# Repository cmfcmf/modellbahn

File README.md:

# Modellbahn

Eine Sammlung von Hardware und Software, die ich auf meiner Modelleisenbahnanlage verwende.

Eine Übersicht über alle Projekte ist hier zu finden: https://cmfcmf.github.io/modellbahn.

Lokal kann man die Website folgendermaßen bauen:

    bundle exec jekyll serve --livereload

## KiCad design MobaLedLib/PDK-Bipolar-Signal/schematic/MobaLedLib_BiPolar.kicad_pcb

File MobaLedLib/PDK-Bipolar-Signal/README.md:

---
layout: project
tags: [padauk, signale, mobaledlib]
permalink: mobaledlib/bipolar-led-driver-pdk
state: finished
---

# MobaLedLib PFS173 Bipolar LED Driver

| Oberseite                   | Unterseite                       |
| --------------------------- | -------------------------------- |
| |  |

Bei diesem Projekt handelt es sich um einen Treiber-Baustein für bipolare LEDs, wie sie z.B. in den Märklin Hobby-Signalen verwendet werden.
Wir benutzen einen sehr kostengünstigen [PFS173](https://free-pdk.github.io/chips/PFS173) Mikrocontroller um das PWM-Signal des roten und grünen Kanals eines WS2811 zu lesen.
Basierend auf diesem Signal generiert der Mikrocontroller an zwei Pins ein komplementäres PWM-Signal.
An diese beiden Ausgänge kann dann eine bipolare LED angeschlossen werden.

Die vier Ausgänge auf der linken Seite des Moduls sind wiefolgt belegt:

| Ausgang   | Funktion                                                      |
| --------- | ------------------------------------------------------------- |
| 1 (oben)  | rote LED +, grüne LED - (bis 20mA, keine Konstantstromquelle) |
| 2         | rote LED -, grüne LED + (bis 20mA, keine Konstantstromquelle) |
| 3         | 5V                                                            |
| 4 (unten) | blauer Kanal (unverändert, direkt vom WS2811)                 |

Auf dem Board befindet sich eine Heartbeat-LED, die fortwährend blinkt.

{%- include pdf_view.html name="schematic/MobaLedLib_BiPolar-Schematic.pdf" -%}
{%- include pdf_view.html name="schematic/MobaLedLib_BiPolar-PCB.pdf" -%}

## Programmierung

Der Mikrocontroller ist mit der [Free-PDK Toolchain](https://free-pdk.github.io/) programmiert.
Zusätzlich benötigt werden die Include-Files von [hier](https://github.com/free-pdk/pdk-includes) und [hier](https://github.com/free-pdk/easy-pdk-includes).

## Lizenz

GPLv2, wobei die Dateien im "code/includes" Ordner von [hier](https://github.com/free-pdk/free-pdk-examples/tree/master/include) stammen.

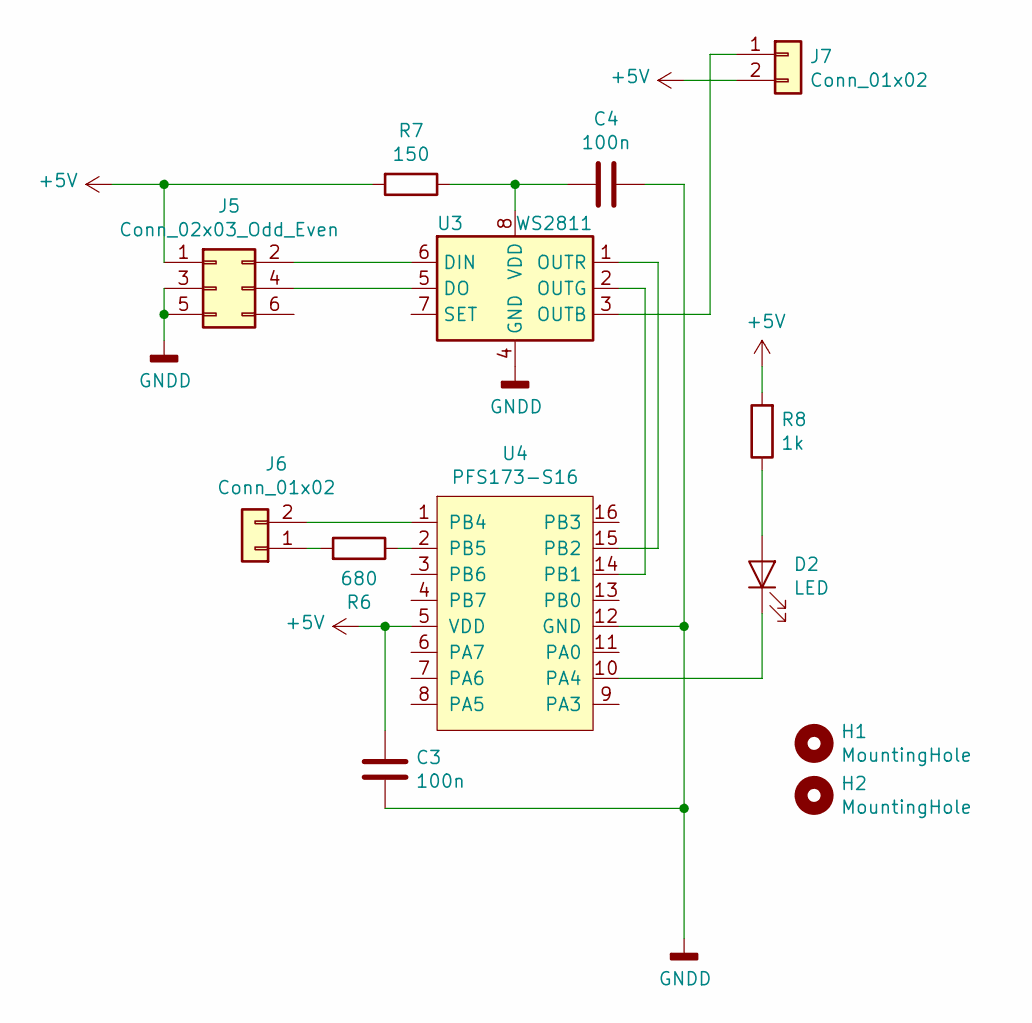
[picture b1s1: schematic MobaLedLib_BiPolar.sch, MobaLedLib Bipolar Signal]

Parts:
C3, C4: 100n; C_Disc_D4.7mm_W2.5mm_P5.00mm
D2: LED; LED_D3.0mm
H1, H2: MountingHole; MountingHole_3.2mm_M3_ISO7380
J5: Conn_02x03_Odd_Even; IDC-Header_2x03_P2.54mm_Vertical
J6, J7: Conn_01x02; TerminalBlock_bornier-2_P5.08mm
R6: 680; R_Axial_DIN0204_L3.6mm_D1.6mm_P2.54mm_Vertical
R7: 150; R_Axial_DIN0204_L3.6mm_D1.6mm_P7.62mm_Horizontal
R8: 1k; R_Axial_DIN0204_L3.6mm_D1.6mm_P2.54mm_Vertical
U3: WS2811; DIP-8_W7.62mm_Socket_LongPads
U4: PFS173-S16; DA04-11SEKWA

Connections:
+5V: C3.1, J5.1, J7.2, R7.2, R8.2, U4.5 (VDD)
GNDD: C3.2, C4.1, J5.3, J5.5, U3.4 (GND), U4.12 (GND)
unnamed: C4.2, R7.1, U3.8 (VDD)
unnamed: D2.1 (K), U4.10 (PA4)
unnamed: D2.2 (A), R8.1
unnamed: J5.2, U3.6 (DIN)
unnamed: J5.4, U3.5 (DO)
unnamed: J6.1, R6.2
unnamed: J6.2, U4.1 (PB4)
unnamed: J7.1, U3.3 (OUTB)
unnamed: R6.1, U4.2 (PB5)
unnamed: U3.1 (OUTR), U4.15 (PB2)
unnamed: U3.2 (OUTG), U4.14 (PB1)

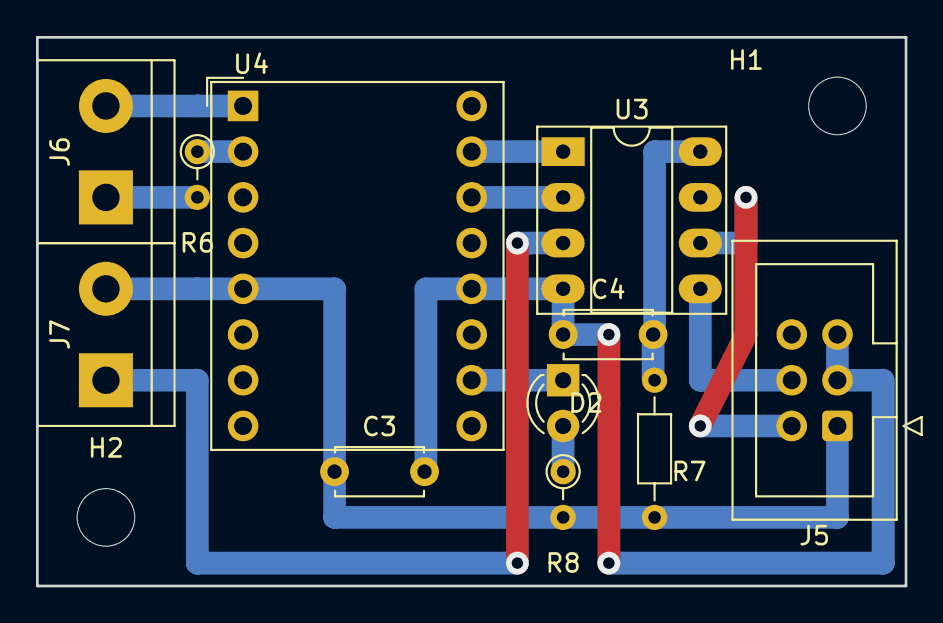
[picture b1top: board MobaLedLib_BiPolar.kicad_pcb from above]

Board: 2 copper layers, 48.3 x 30.5 mm, 13 parts (0 on the bottom side), 13 nets.

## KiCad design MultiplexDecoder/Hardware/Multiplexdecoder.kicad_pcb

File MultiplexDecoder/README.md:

---
layout: project
tags: [arduino, arduino nano, decoder, signale, viessmann, dcc]
permalink: decoder/multiplex
state: wip
related_projects: [signale/multiplex]
---

# Decoder für Viessmann Multiplex-Signale

Es handelt sich um einen DCC-Decoder für 4 Multiplex-Signale von Viessmann.
Der Decoder basiert auf einem Arduino Nano.

## Funktionen

- Ansteuerung von bis zu 4 HV-Signalen, jeweils optional mit Vorsignal am Mast
  - KS-Signale wären theoretisch auch möglich, sind aber noch nicht implementiert, da ich keine zum Testen da habe
- Automatische Erkennung der Signaltypen beim Einschalten
- Alle Signalbilder schaltbar, inklusive "dunkel"
- Sanftes Überblenden zwischen den Signalbildern
- Steuerung über DCC-Weichenbefehle
- Separate Adressen pro Signal und Vorsignal

### Adresseinstellung

1. ggf. neue Signale anschließen und den Dekoder neu starten,
   indem der Reset-Knopf auf der Arduino-Platine gedruckt wird.
   Dadurch werden die neu angeschlossenen Signale erkannt.
2. Es darf nun kein Fahrbetrieb mehr stattfinden und keine (anderen) Weichen und Signale geschaltet werden!
3. Den Adressprogrammierknopf einmal drücken -> die LED auf der Platine fängt an zu blinken.
4. Das erste angeschlossene Hauptsignal fängt an, nacheinander alle Signalbilder durchzuschalten.
5. Möchte man die Adresse des Signals nicht ändern, drückt man einfach den Adressprogrammierknopf nochmal.
   Andernfalls sendet man einen Weichenbefehl mit der Digitalzentrale. Das Signal übernimmt dann die gesendete Adresse.
6. Jetzt fängt das nächste Signal an alle Signalbilder durchzuschalten. War am Mast des Hauptsignals ein
   Vorsignal angeschlossen, fängt dieses an die Signalbilder durchzuschalten.
7. Nun sendet man die Adresse des nächsten Signals wie in Schritt 5 beschrieben.
8. Wenn alle angeschlossenen Signale neue Adressen erhalten haben, hört die LED auf der Platine auf zu blinken.

## Hardware

Der Schaltplan ist sehr einfach gehalten und bietet Anschlussmöglichkeiten für sowohl
die Stecker der Viessmann-Signale als auch eigene Verlängerungsleitungen. In allen
Signalleitungen sind 680Ω-Widerstände verbaut. Damit leuchten die Signale immer noch
sehr hell. Das DCC-Signal wird über einen 6N137-Optokoppler eingelesen.
Die Stromversorgung geschieht an einem separaten Eingang über einen Gleichrichter
mit nachgeschaltetem 7805-Linearregler. Man kann beide Eingänge auch parallel schalten,
wenn man keine separate Stromversorgung benutzen möchte.
Der Programmierknopf ist an A6 angeschlossen. Da dieser Eingang nicht über einen
internen Pull-Up-Widerstand verfügt, ist dieser extern vorgesehen.

{%- include pdf_view.html name="Hardware/Multiplexdecoder.pdf" -%}

Eine abgespeckte Version der Platine habe ich derzeit auf Lochraster aufgebaut.
Aufgrund der einfachen Schaltung ging das flott von der Hand. Eine "professionell"
gelayoutete Platine habe ich ebenfalls erstellt, aber noch nicht fertigen lassen
(der Arduino fehlt im 3D-Bild):

{%- include image_view.html name="Hardware/Multiplexdecoder.png" -%}

## Software

Die Software ist für die Arduino-IDE geschrieben und muss mittels dieser in den
Arduino Nano übertragen werden. Falls die Übertragung nicht funktioniert, sollte
man nochmal sichergehen, dass im Menü unter `Werkzeuge -> Board` `Arduino Nano`
ausgewählt und unter `Werkzeuge -> Prozessor` `Atmega328P` oder `Atmega328P (Old Bootloader)`
ausgewählt ist. Ob der Bootloader des Arduinos neu oder "old" ist, lässt sich
am besten durch probieren herausfinden; wenn die Übertragung klappt, hat man
den richtigen Eintrag ausgewählt.

### Konfigurationsoptionen

Einige Optionen sind nur beim Programmieren des Arduinos und nicht im
späteren Betrieb einstellbar. Die notwendigen Einstellungen befinden sich
allesamt in der `Config.h`-Datei und müssen angepasst werden, bevor der
Arduino programmiert wird.

- **DEMO**
  - **0**: Normaler Betrieb
  - **1**: Demomodus aktiv: Alle Signale schalten nacheinander automatisch ihre Signalbegriffe durch.
  - **2**: Demomodus aktiv: Alle Signale schalten zufällige Signalbegriffe durcheinander.
- **DARK_MAIN_SIGNAL_ASPECT**
  - **0**: Hauptsignale können nicht dunkel geschaltet werden.
  - **1**: Hauptsignale können zusätzlich dunkel geschaltet werden.
- **DARK_DISTANT_SIGNAL_ASPECT**
  - **0**: Vorsignale können nicht dunkel geschaltet werden
    (**steht das Hauptsignal auf rot, wird das Vorsignal aber in jedem Fall dunkel geschaltet!**).
  - **1**: Vorsignale können zusätzlich dunkel geschaltet werden.
- **USE_SERIAL**
  - **0**: Keine Debug-Ausgaben über den seriellen Anschluss.
  - **1**: Zusätzliche Debug-Ausgaben über den seriellen Anschluss.

{%- include code_view.html name="Config.h" from_line=4 to_line=8 -%}

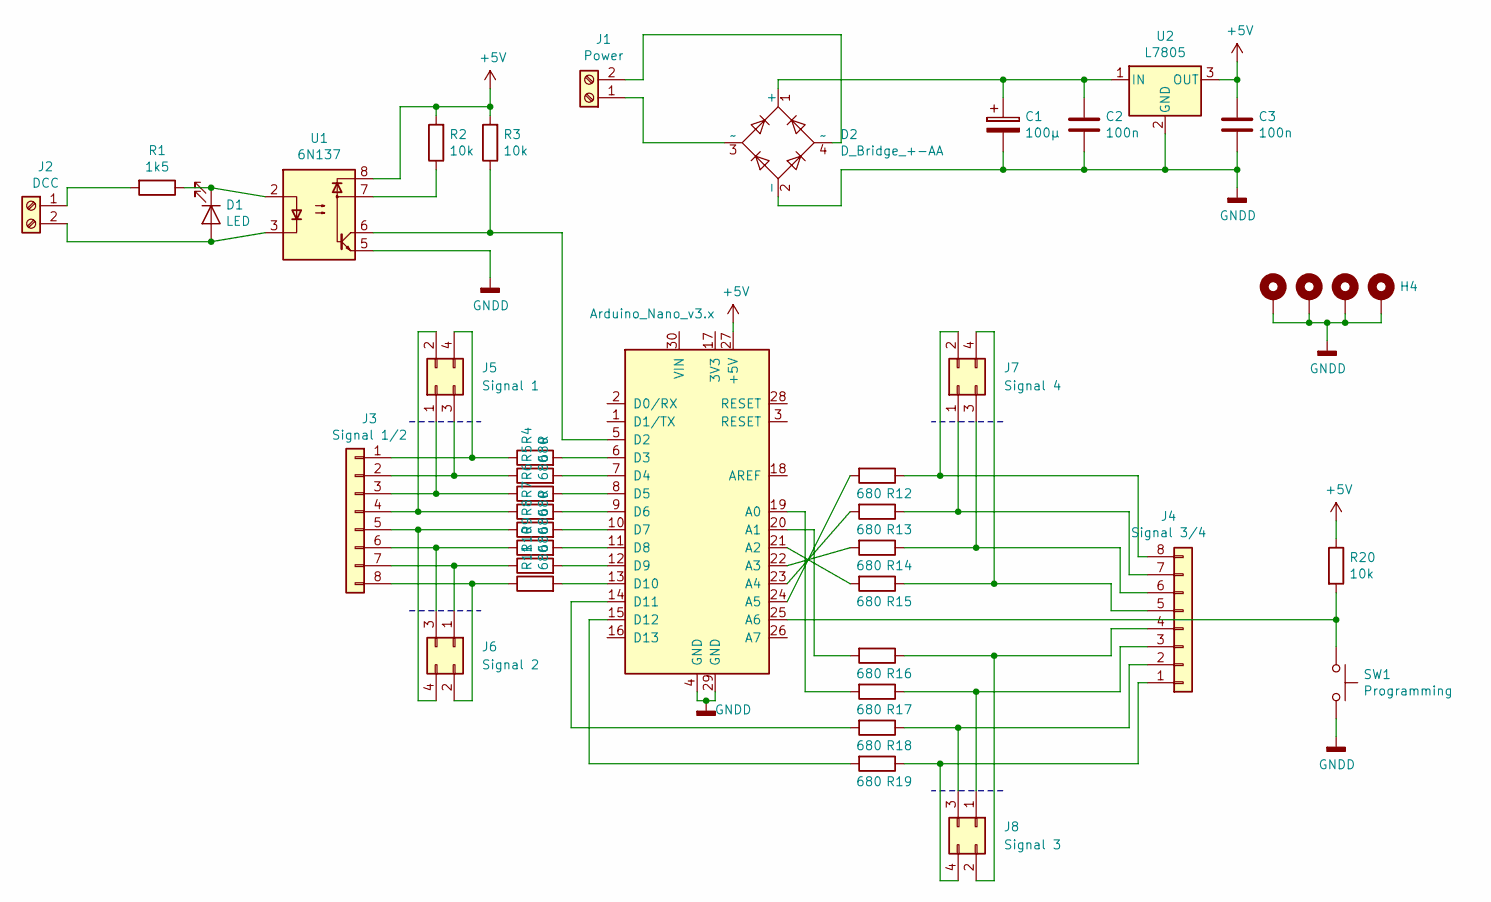
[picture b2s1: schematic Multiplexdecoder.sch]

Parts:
A1: Arduino_Nano_v3.x; Arduino_Nano
C1: 100µ; CP_Radial_D10.0mm_P5.00mm
C2, C3: 100n; C_Disc_D4.3mm_W1.9mm_P5.00mm
D1: LED; LED_D3.0mm
D2: D_Bridge_+-AA; Diode_Bridge_DIP-4_W7.62mm_P5.08mm
H1, H2, H3, H4: MountingHole_Pad; MountingHole_3.2mm_M3_Pad_Via
J1: Power; PhoenixContact_MSTBA_2,5_2-G-5,08_1x02_P5.08mm_Horizontal
J2: DCC; PhoenixContact_MSTBA_2,5_2-G-5,08_1x02_P5.08mm_Horizontal
J3: Signal 1/2; PhoenixContact_MSTBA_2,5_8-G-5,08_1x08_P5.08mm_Horizontal
J4: Signal 3/4; PhoenixContact_MSTBA_2,5_8-G-5,08_1x08_P5.08mm_Horizontal
J5: Signal 1; PinHeader_2x02_P2.00mm_Vertical
J6: Signal 2; PinHeader_2x02_P2.00mm_Vertical
J7: Signal 4; PinHeader_2x02_P2.00mm_Vertical
J8: Signal 3; PinHeader_2x02_P2.00mm_Vertical
R1: 1k5; R_Axial_DIN0204_L3.6mm_D1.6mm_P5.08mm_Horizontal
R2, R3, R20: 10k; R_Axial_DIN0204_L3.6mm_D1.6mm_P5.08mm_Horizontal
R4, R7: R; R_Axial_DIN0204_L3.6mm_D1.6mm_P1.90mm_Vertical
R5, R6, R8, R9, R10, R11, R12, R13, R14, R15, R16, R17, R18, R19: 680; R_Axial_DIN0204_L3.6mm_D1.6mm_P1.90mm_Vertical
SW1: Programming; SW_PUSH_6mm_H5mm
U1: 6N137; DIP-8_W7.62mm
U2: L7805; TO-220-3_Vertical

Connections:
+5V: A1.27 (+5V), C3.1, R2.2, R3.2, R20.1, U1.8, U2.3 (OUT)
GNDD: A1.4 (GND), A1.29 (GND), C1.2, C2.2, C3.2, D2.2 (-), H1.1, H2.1, H3.1, H4.1, SW1.2, U1.5, U2.2 (GND)
unnamed: A1.5 (D2), R3.1, U1.6
unnamed: A1.6 (D3), R4.2
unnamed: A1.7 (D4), R5.2
unnamed: A1.8 (D5), R6.2
unnamed: A1.9 (D6), R7.2
unnamed: A1.10 (D7), R8.2
unnamed: A1.11 (D8), R9.2
unnamed: A1.12 (D9), R10.2
unnamed: A1.13 (D10), R11.2
unnamed: A1.14 (D11), R18.2
unnamed: A1.15 (D12), R19.2
unnamed: A1.19 (A0), R17.2
unnamed: A1.20 (A1), R16.2
unnamed: A1.21 (A2), R15.2
unnamed: A1.22 (A3), R14.2
unnamed: A1.23 (A4), R13.2
unnamed: A1.24 (A5), R12.2
unnamed: A1.25 (A6), R20.2, SW1.1
unnamed: C1.1, C2.1, D2.1 (+), U2.1 (IN)
unnamed: D1.1 (K), R1.1, U1.2
unnamed: D1.2 (A), J2.2, U1.3
unnamed: D2.3 (~~), J1.1
unnamed: D2.4 (~~), J1.2
unnamed: J2.1, R1.2
unnamed: J3.1, J5.4, R4.1
unnamed: J3.2, J5.3, R5.1
unnamed: J3.3, J5.1, R6.1
unnamed: J3.4, J5.2, R7.1
unnamed: J3.5, J6.4, R8.1
unnamed: J3.6, J6.3, R9.1
unnamed: J3.7, J6.1, R10.1
unnamed: J3.8, J6.2, R11.1
unnamed: J4.1, J8.4, R19.1
unnamed: J4.2, J8.3, R18.1
unnamed: J4.3, J8.1, R17.1
unnamed: J4.4, J8.2, R16.1
unnamed: J4.5, J7.4, R15.1
unnamed: J4.6, J7.3, R14.1
unnamed: J4.7, J7.1, R13.1
unnamed: J4.8, J7.2, R12.1
unnamed: R2.1, U1.7

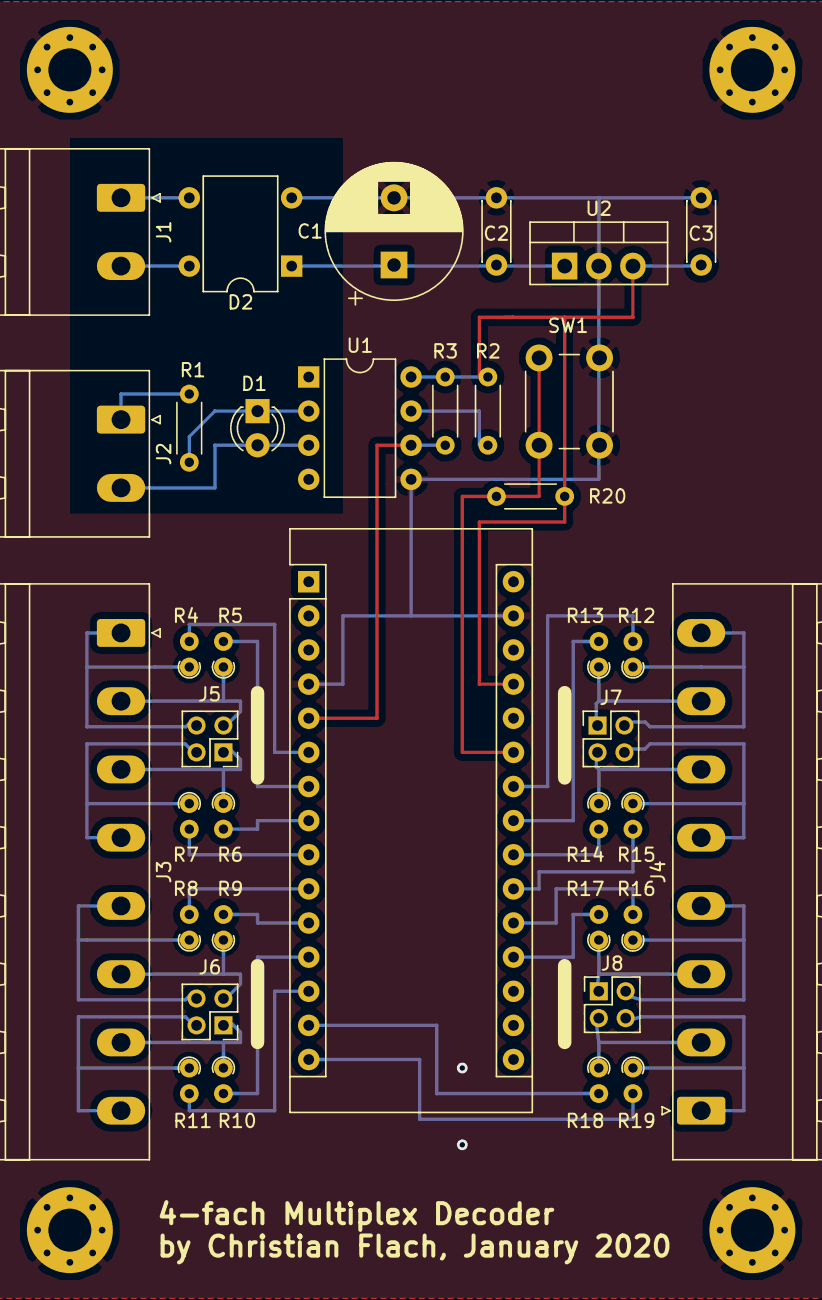
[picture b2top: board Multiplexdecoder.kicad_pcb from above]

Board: 2 copper layers, 41 parts (0 on the bottom side), 43 nets.

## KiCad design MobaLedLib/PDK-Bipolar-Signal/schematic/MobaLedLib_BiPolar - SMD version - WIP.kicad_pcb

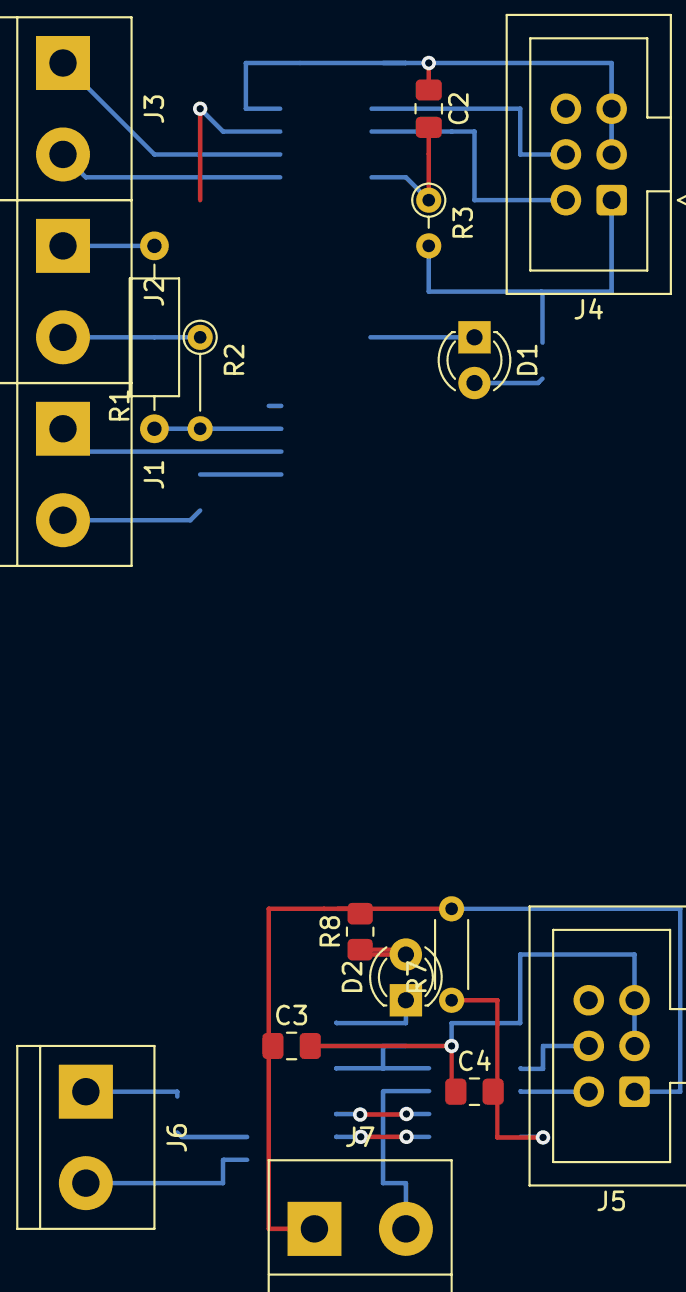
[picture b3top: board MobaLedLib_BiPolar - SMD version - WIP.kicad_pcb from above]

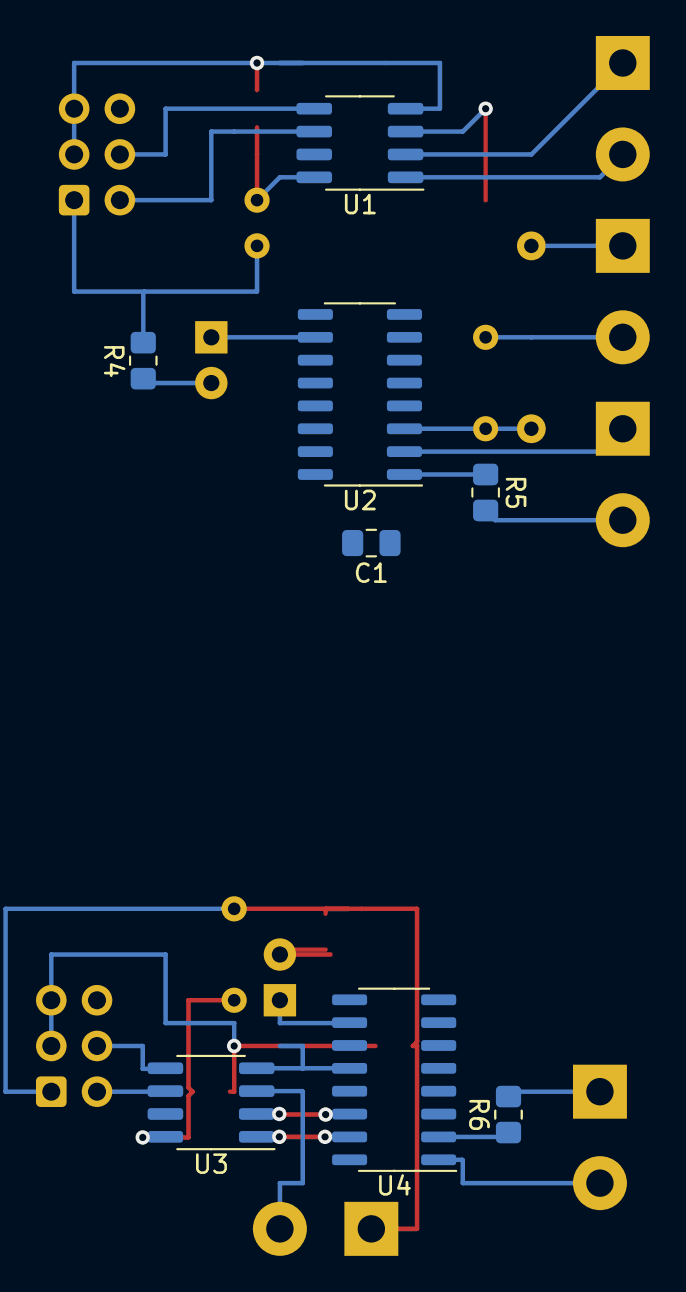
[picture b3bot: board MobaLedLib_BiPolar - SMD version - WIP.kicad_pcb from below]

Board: 2 copper layers, 25 parts (8 on the bottom side), 26 nets.

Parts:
C1, C2, C3, C4: 100n; C_0805_2012Metric_Pad1.18x1.45mm_HandSolder
D1, D2: LED; LED_D3.0mm
J1, J2, J3, J6, J7: Conn_01x02; TerminalBlock_bornier-2_P5.08mm
J4, J5: Conn_02x03_Odd_Even; IDC-Header_2x03_P2.54mm_Vertical
R1: 150k; R_Axial_DIN0207_L6.3mm_D2.5mm_P10.16mm_Horizontal
R2: 22k; R_Axial_DIN0204_L3.6mm_D1.6mm_P5.08mm_Vertical
R3: 150; R_Axial_DIN0204_L3.6mm_D1.6mm_P2.54mm_Vertical
R4, R8: 1k; R_0805_2012Metric_Pad1.20x1.40mm_HandSolder
R5, R6: 680; R_0805_2012Metric_Pad1.20x1.40mm_HandSolder
R7: 150; R_Axial_DIN0204_L3.6mm_D1.6mm_P5.08mm_Horizontal
U1, U3: WS2811; SOP-8_3.76x4.96mm_P1.27mm
U2, U4: PFS173-S16; SOIC-16_3.9x9.9mm_P1.27mm

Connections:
+5V: C3.1, J2.1, J4.1, J5.1, J7.1, R1.2, R3.2, R4.2, R7.2, R8.2, U2.4, U4.5
GNDD: C1.2, C2.1, C3.2, C4.1, J2.2, J4.3, J4.5, J5.3, J5.5, R2.1, U1.4, U2.12, U3.4, U4.12
unnamed: C1.1, U2.5
unnamed: C2.2, R3.1, U1.8
unnamed: C4.2, R7.1, U3.8
unnamed: D1.1, U2.10
unnamed: D1.2, R4.1
unnamed: D2.1, U4.10
unnamed: D2.2, R8.1
unnamed: J1.1, U2.2
unnamed: J1.2, R5.2
unnamed: J3.1, U1.2
unnamed: J3.2, U1.1
unnamed: J4.2, U1.6
unnamed: J4.4, U1.5
unnamed: J5.2, U3.6
unnamed: J5.4, U3.5
unnamed: J6.1, R6.2
unnamed: J6.2, U4.1
unnamed: J7.2, U3.3
unnamed: R1.1, R2.2, U2.3
unnamed: R5.1, U2.1
unnamed: R6.1, U4.2
unnamed: U1.3, U2.13
unnamed: U3.1, U4.15
unnamed: U3.2, U4.14

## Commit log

2019-12-27 Initial commit.
2019-12-27 Add jekyll site
2019-12-27 Infos zur Wagenbeleuchtung
2019-12-27 Fix support for serving from subdirectory
2019-12-27 Use GitHub's STL viewer
2019-12-27 Add mathjax support
2019-12-27 Allgemeines zur Wagenbeleuchtung
2019-12-27 Sortiere Projekte nach Titel
2019-12-29 Minor site improvements
2019-12-29 Add section on multiplex signals
2019-12-29 Fix language, add sitemap
2019-12-29 Add support for project states
2019-12-30 Introduce "related projects"
2019-12-30 Fix typo
2019-12-30 Add privacy policy link
2019-12-30 Import MultiplexDecoder project
2019-12-30 Add code highlighting support
2019-12-30 Performance improvements, do not persist state in demo mode
2019-12-31 Make Serial and dark aspects optional, use watchdog as coarse timer
2019-12-31 Allow separate addresses per signal, improve address programming experience
2019-12-31 Show filename in code box footer
2020-01-01 Detect some file types from file content
2020-01-01 Improve documentation
2020-01-01 Adjust pin mapping for board layout
2020-01-01 Create schematic and pcb with KiCad
2020-01-01 Document hardware
2020-01-04 Split up dimming updates across multiple invocations of the ISR
    This makes it less likely that an INT0 edge may be missed
2020-01-04 Add makefile and proof of concept test using simulavr
2020-01-04 Fix signal aspect order to match what the CS2 expects
2020-01-04 Move templates into .h to be Arduino IDE-compatible
2020-01-05 Add information on dccpp
2020-01-05 Minor fixes
2020-02-06 Add state: finished to Schleppschalter Umbau
2020-02-26 Bump nokogiri from 1.10.7 to 1.10.8
    Bumps [nokogiri](https://github.com/sparklemotion/nokogiri) from 1.10.7 to 1.10.8.
    - [Release notes](https://github.com/sparklemotion/nokogiri/releases)
    - [Changelog](https://github.com/sparklemotion/nokogiri/blob/master/CHANGELOG.md)
    - [Commits](https://github.com/sparklemotion/nokogiri/compare/v1.10.7...v1.10.8)
2020-05-26 Bump activesupport from 6.0.2.1 to 6.0.3.1
    Bumps [activesupport](https://github.com/rails/rails) from 6.0.2.1 to 6.0.3.1.
    - [Release notes](https://github.com/rails/rails/releases)
    - [Changelog](https://github.com/rails/rails/blob/v6.0.3.1/activesupport/CHANGELOG.md)
    - [Commits](https://github.com/rails/rails/compare/v6.0.2.1...v6.0.3.1)
2020-07-29 Start working on an EP2C5T144 tutorial
2020-08-11 More tutorial steps
2021-02-02 Update dependencies
2021-02-02 Blue Pill Docs
2021-02-10 Fix formatting
2021-03-26 Add TinyUniProg pcb
2021-03-26 Fixes + images
2021-03-28 Create MobaLedLib subdirectory
2021-03-28 Add PDK bipolar signal driver
2021-03-28 Fix tags
2021-04-30 Bump rexml from 3.2.4 to 3.2.5
    Bumps [rexml](https://github.com/ruby/rexml) from 3.2.4 to 3.2.5.
    - [Release notes](https://github.com/ruby/rexml/releases)
    - [Changelog](https://github.com/ruby/rexml/blob/master/NEWS.md)
    - [Commits](https://github.com/ruby/rexml/compare/v3.2.4...v3.2.5)
2021-05-04 Fix image urls
2021-05-20 Bump nokogiri from 1.11.1 to 1.11.5
    Bumps [nokogiri](https://github.com/sparklemotion/nokogiri) from 1.11.1 to 1.11.5.
    - [Release notes](https://github.com/sparklemotion/nokogiri/releases)
    - [Changelog](https://github.com/sparklemotion/nokogiri/blob/main/CHANGELOG.md)
    - [Commits](https://github.com/sparklemotion/nokogiri/compare/v1.11.1...v1.11.5)
2021-07-13 Bump addressable from 2.7.0 to 2.8.0
    Bumps [addressable](https://github.com/sporkmonger/addressable) from 2.7.0 to 2.8.0.
    - [Release notes](https://github.com/sporkmonger/addressable/releases)
    - [Changelog](https://github.com/sporkmonger/addressable/blob/main/CHANGELOG.md)
    - [Commits](https://github.com/sporkmonger/addressable/compare/addressable-2.7.0...addressable-2.8.0)
    ---
    updated-dependencies:
2021-09-28 Bump nokogiri from 1.11.5 to 1.12.5
    Bumps [nokogiri](https://github.com/sparklemotion/nokogiri) from 1.11.5 to 1.12.5.
    - [Release notes](https://github.com/sparklemotion/nokogiri/releases)
    - [Changelog](https://github.com/sparklemotion/nokogiri/blob/main/CHANGELOG.md)
    - [Commits](https://github.com/sparklemotion/nokogiri/compare/v1.11.5...v1.12.5)
    ---
    updated-dependencies:
2022-02-26 Bump nokogiri from 1.12.5 to 1.13.3
    Bumps [nokogiri](https://github.com/sparklemotion/nokogiri) from 1.12.5 to 1.13.3.
    - [Release notes](https://github.com/sparklemotion/nokogiri/releases)
    - [Changelog](https://github.com/sparklemotion/nokogiri/blob/main/CHANGELOG.md)
    - [Commits](https://github.com/sparklemotion/nokogiri/compare/v1.12.5...v1.13.3)
    ---
    updated-dependencies:
2022-04-12 Bump nokogiri from 1.12.5 to 1.13.4
    Bumps [nokogiri](https://github.com/sparklemotion/nokogiri) from 1.12.5 to 1.13.4.
    - [Release notes](https://github.com/sparklemotion/nokogiri/releases)
    - [Changelog](https://github.com/sparklemotion/nokogiri/blob/v1.13.4/CHANGELOG.md)
    - [Commits](https://github.com/sparklemotion/nokogiri/compare/v1.12.5...v1.13.4)
    ---
    updated-dependencies:
2022-05-18 Bump nokogiri from 1.12.5 to 1.13.6
    Bumps [nokogiri](https://github.com/sparklemotion/nokogiri) from 1.12.5 to 1.13.6.
    - [Release notes](https://github.com/sparklemotion/nokogiri/releases)
    - [Changelog](https://github.com/sparklemotion/nokogiri/blob/main/CHANGELOG.md)
    - [Commits](https://github.com/sparklemotion/nokogiri/compare/v1.12.5...v1.13.6)
    ---
    updated-dependencies:
2022-07-22 Bump tzinfo from 1.2.9 to 1.2.10
    Bumps [tzinfo](https://github.com/tzinfo/tzinfo) from 1.2.9 to 1.2.10.
    - [Release notes](https://github.com/tzinfo/tzinfo/releases)
    - [Changelog](https://github.com/tzinfo/tzinfo/blob/master/CHANGES.md)
    - [Commits](https://github.com/tzinfo/tzinfo/compare/v1.2.9...v1.2.10)
    ---
    updated-dependencies:
2022-10-20 Bump nokogiri from 1.12.5 to 1.13.9
    Bumps [nokogiri](https://github.com/sparklemotion/nokogiri) from 1.12.5 to 1.13.9.
    - [Release notes](https://github.com/sparklemotion/nokogiri/releases)
    - [Changelog](https://github.com/sparklemotion/nokogiri/blob/main/CHANGELOG.md)
    - [Commits](https://github.com/sparklemotion/nokogiri/compare/v1.12.5...v1.13.9)
    ---
    updated-dependencies:
2023-01-31 Bump activesupport from 6.0.3.4 to 6.0.6.1
    Bumps [activesupport](https://github.com/rails/rails) from 6.0.3.4 to 6.0.6.1.
    - [Release notes](https://github.com/rails/rails/releases)
    - [Changelog](https://github.com/rails/rails/blob/v7.0.4.2/activesupport/CHANGELOG.md)
    - [Commits](https://github.com/rails/rails/compare/v6.0.3.4...v6.0.6.1)
    ---
    updated-dependencies:
2023-04-12 Bump nokogiri from 1.12.5 to 1.14.3
    Bumps [nokogiri](https://github.com/sparklemotion/nokogiri) from 1.12.5 to 1.14.3.
    - [Release notes](https://github.com/sparklemotion/nokogiri/releases)
    - [Changelog](https://github.com/sparklemotion/nokogiri/blob/main/CHANGELOG.md)
    - [Commits](https://github.com/sparklemotion/nokogiri/compare/v1.12.5...v1.14.3)
    ---
    updated-dependencies:
